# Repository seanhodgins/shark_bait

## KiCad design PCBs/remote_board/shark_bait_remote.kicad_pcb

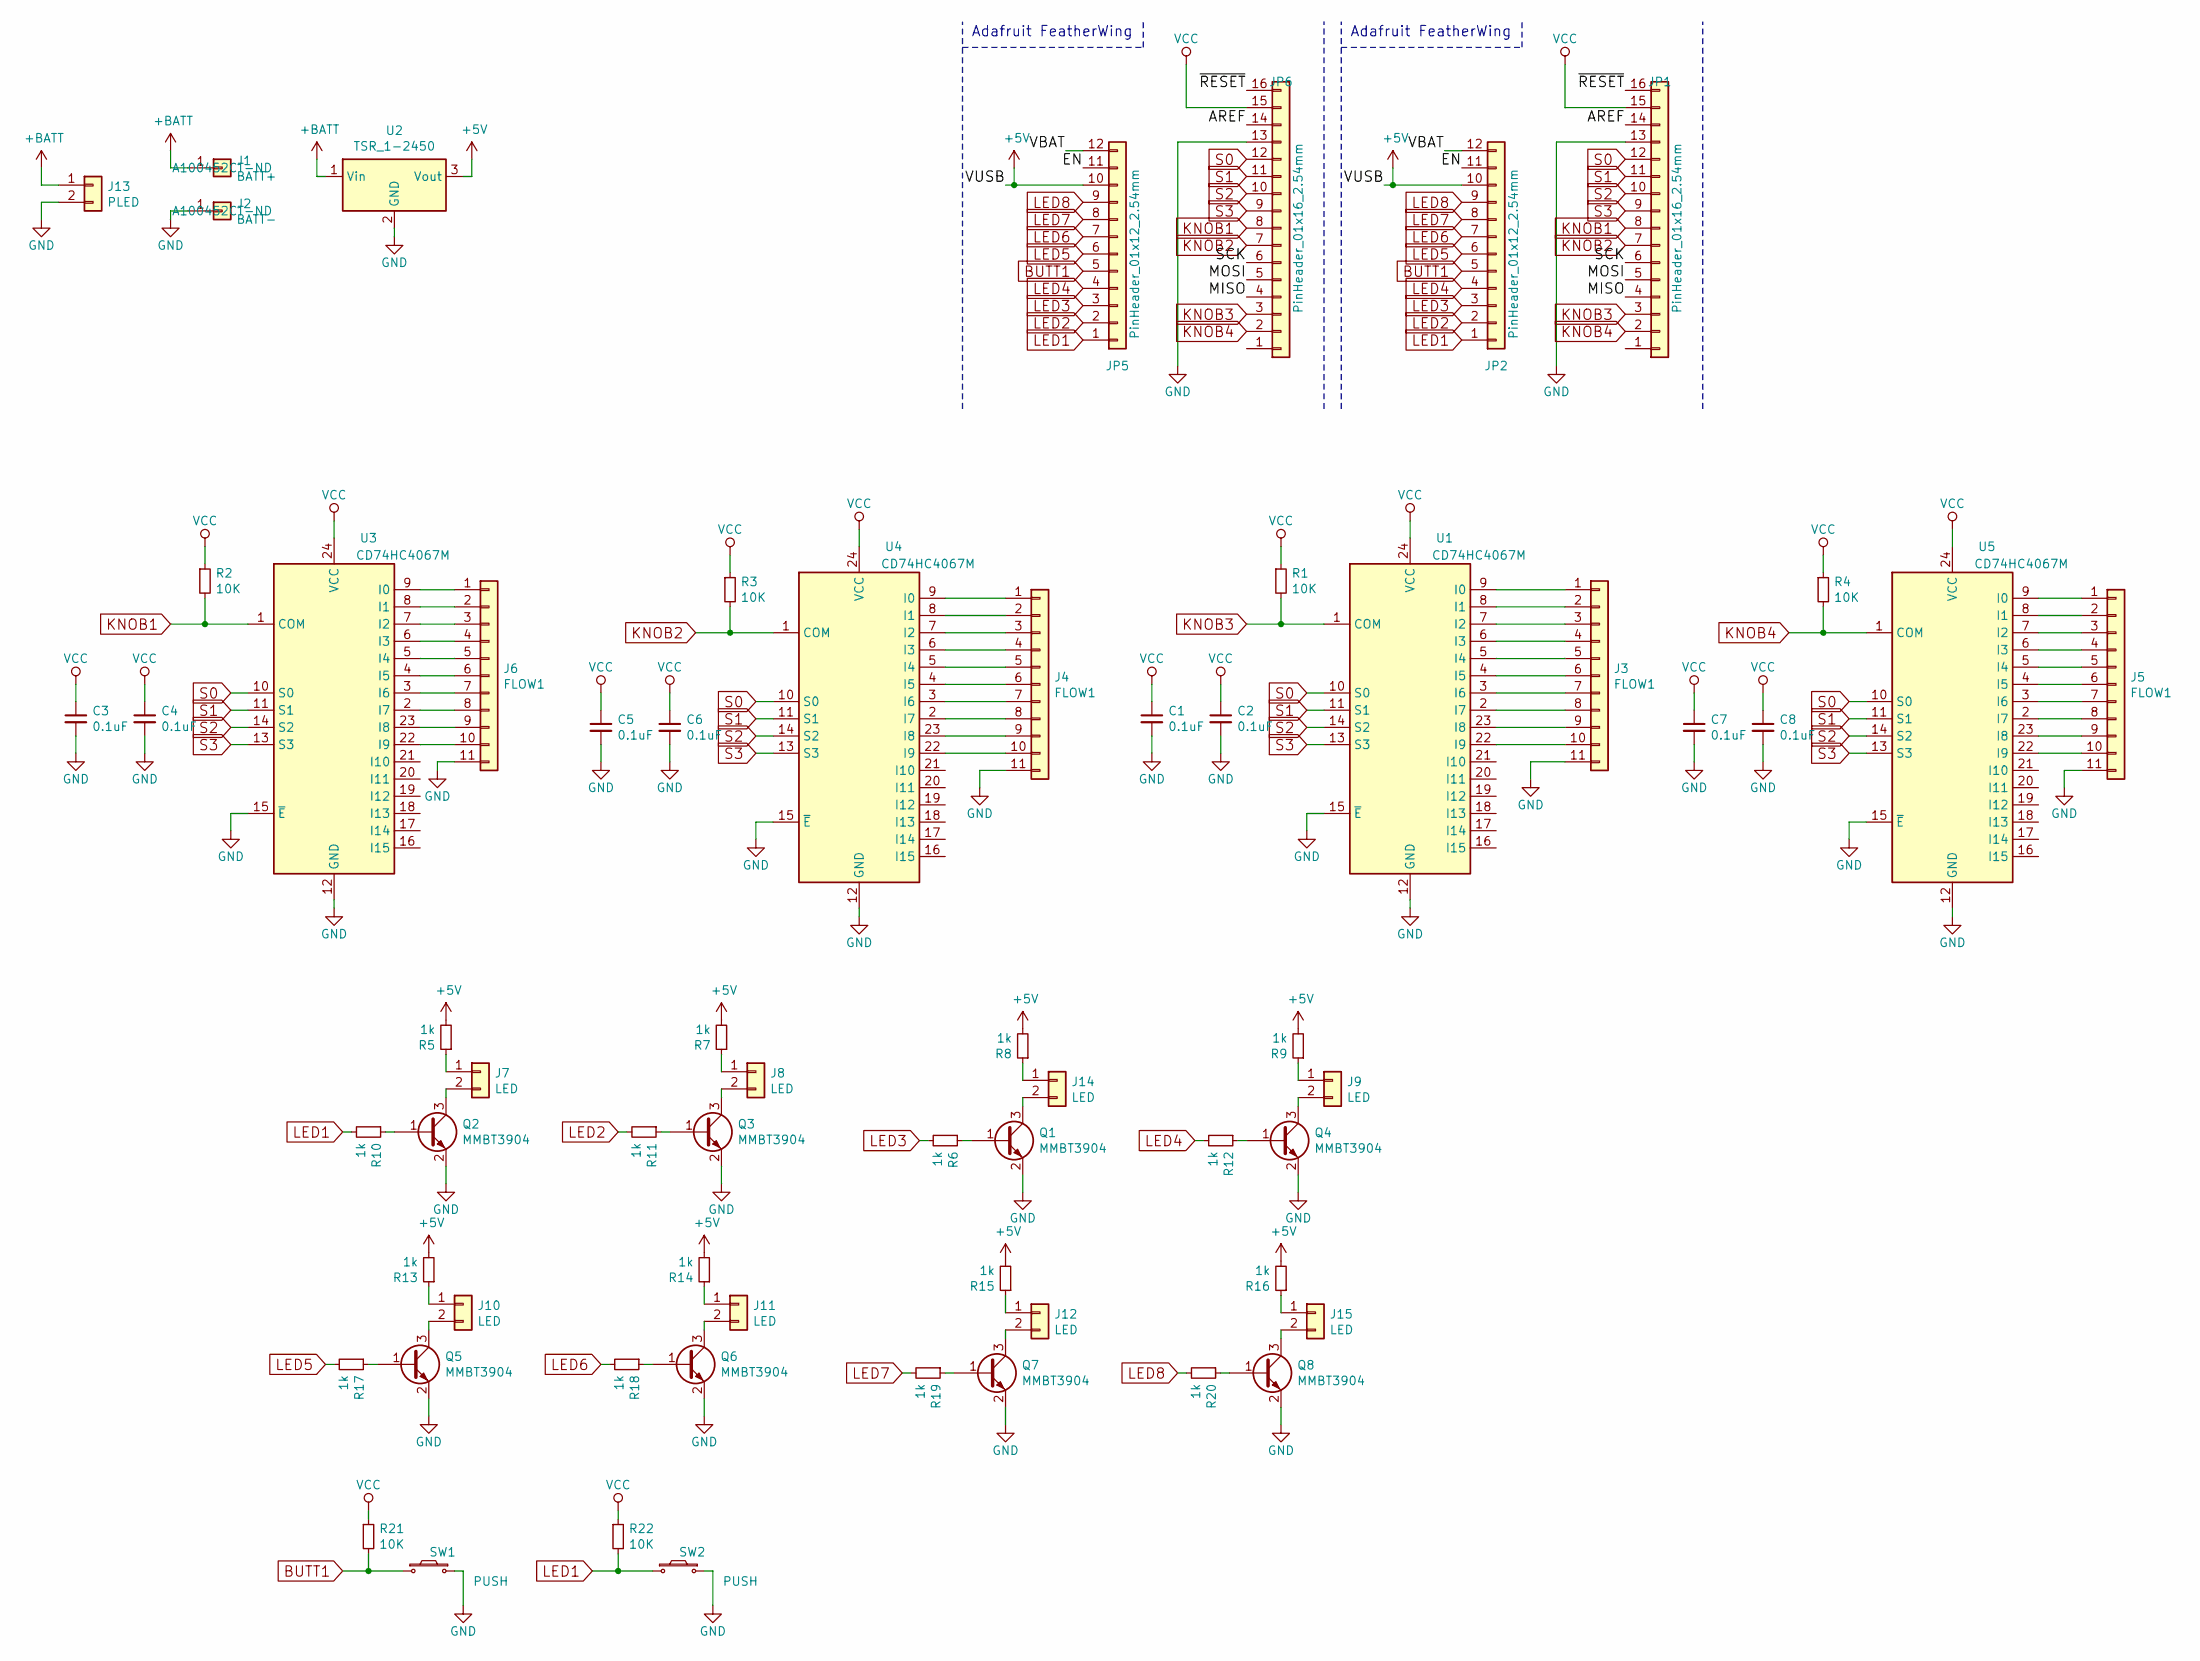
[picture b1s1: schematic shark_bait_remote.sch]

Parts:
C1, C2, C3, C4, C5, C6, C7, C8: 0.1uF; C_0805_2012Metric
J1: BATT+; connect_QC_Male; Digikey Part No. A100452CT-ND
J2: BATT-; connect_QC_Male; Digikey Part No. A100452CT-ND
J3, J4, J5, J6: FLOW1; JST_PH_B11B-PH-K_1x11_P2.00mm_Vertical
J7, J8, J9, J10, J11, J12, J14, J15: LED; JST_PH_B2B-PH-K_1x02_P2.00mm_Vertical
J13: PLED; JST_PH_B2B-PH-K_1x02_P2.00mm_Vertical
JP1, JP6: PinHeader_01x16_2.54mm; Conn_PinHeader_1x16_Reduced
JP2, JP5: PinHeader_01x12_2.54mm; Conn_PinHeader_1x12_Reduced
Q1, Q2, Q3, Q4, Q5, Q6, Q7, Q8: MMBT3904; SOT-23
R1, R2, R3, R4, R21, R22: 10K; R_0805_2012Metric
R5, R6, R7, R8, R9, R10, R11, R12, R13, R14, R15, R16, R17, R18, R19, R20: 1k; R_0805_2012Metric
SW1, SW2: PUSH; JST_PH_B2B-PH-K_1x02_P2.00mm_Vertical
U1, U3, U4, U5: CD74HC4067M; SOIC-24W_7.5x15.4mm_P1.27mm; Digikey Part No. 296-29408-1-ND
U2: TSR_1-2450; Converter_DCDC_TRACO_TSR-1_THT

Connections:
+5V: JP2.10, JP5.10, R5.2, R7.2, R8.2, R9.2, R13.2, R14.2, R15.2, R16.2, U2.3 (Vout)
+BATT: J1.1, J13.1, U2.1 (Vin)
/AREF: JP1.14, JP6.14
/EN: JP2.11, JP5.11
/MISO: JP1.4, JP6.4
/MOSI: JP1.5, JP6.5
/SCK: JP1.6, JP6.6
/VBAT: JP2.12, JP5.12
/~RESET: JP1.16, JP6.16
BUTT1: JP2.5, JP5.5, R21.2, SW1.1
GND: C1.2, C2.2, C3.2, C4.2, C5.2, C6.2, C7.2, C8.2, J2.1, J3.11, J4.11, J5.11, J6.11, J13.2, JP1.1, JP1.13, JP6.1, JP6.13, Q1.2 (E), Q2.2 (E), Q3.2 (E), Q4.2 (E), Q5.2 (E), Q6.2 (E), Q7.2 (E), Q8.2 (E), SW1.2, SW2.2, U1.12 (GND), U1.15 (~E), U2.2 (GND), U3.12 (GND), U3.15 (~E), U4.12 (GND), U4.15 (~E), U5.12 (GND), U5.15 (~E)
KNOB1: JP1.8, JP6.8, R2.2, U3.1 (COM)
KNOB2: JP1.7, JP6.7, R3.2, U4.1 (COM)
KNOB3: JP1.3, JP6.3, R1.2, U1.1 (COM)
KNOB4: JP1.2, JP6.2, R4.2, U5.1 (COM)
LED1: JP2.1, JP5.1, R10.2, R22.2, SW2.1
LED2: JP2.2, JP5.2, R11.2
LED3: JP2.3, JP5.3, R6.2
LED4: JP2.4, JP5.4, R12.2
LED5: JP2.6, JP5.6, R17.2
LED6: JP2.7, JP5.7, R18.2
LED7: JP2.8, JP5.8, R19.2
LED8: JP2.9, JP5.9, R20.2
unnamed: J3.1, U1.9 (I0)
unnamed: J3.2, U1.8 (I1)
unnamed: J3.3, U1.7 (I2)
unnamed: J3.4, U1.6 (I3)
unnamed: J3.5, U1.5 (I4)
unnamed: J3.6, U1.4 (I5)
unnamed: J3.7, U1.3 (I6)
unnamed: J3.8, U1.2 (I7)
unnamed: J3.9, U1.23 (I8)
unnamed: J3.10, U1.22 (I9)
unnamed: J4.1, U4.9 (I0)
unnamed: J4.2, U4.8 (I1)
unnamed: J4.3, U4.7 (I2)
unnamed: J4.4, U4.6 (I3)
unnamed: J4.5, U4.5 (I4)
unnamed: J4.6, U4.4 (I5)
unnamed: J4.7, U4.3 (I6)
unnamed: J4.8, U4.2 (I7)
unnamed: J4.9, U4.23 (I8)
unnamed: J4.10, U4.22 (I9)
unnamed: J5.1, U5.9 (I0)
unnamed: J5.2, U5.8 (I1)
unnamed: J5.3, U5.7 (I2)
unnamed: J5.4, U5.6 (I3)
unnamed: J5.5, U5.5 (I4)
unnamed: J5.6, U5.4 (I5)
unnamed: J5.7, U5.3 (I6)
unnamed: J5.8, U5.2 (I7)
unnamed: J5.9, U5.23 (I8)
unnamed: J5.10, U5.22 (I9)
unnamed: J6.1, U3.9 (I0)
unnamed: J6.2, U3.8 (I1)
unnamed: J6.3, U3.7 (I2)
unnamed: J6.4, U3.6 (I3)
unnamed: J6.5, U3.5 (I4)
unnamed: J6.6, U3.4 (I5)
unnamed: J6.7, U3.3 (I6)
unnamed: J6.8, U3.2 (I7)
unnamed: J6.9, U3.23 (I8)
unnamed: J6.10, U3.22 (I9)
unnamed: J7.1, R5.1
unnamed: J7.2, Q2.3 (C)
unnamed: J8.1, R7.1
unnamed: J8.2, Q3.3 (C)
unnamed: J9.1, R9.1
unnamed: J9.2, Q4.3 (C)
unnamed: J10.1, R13.1
unnamed: J10.2, Q5.3 (C)
unnamed: J11.1, R14.1
unnamed: J11.2, Q6.3 (C)
unnamed: J12.1, R15.1
unnamed: J12.2, Q7.3 (C)
unnamed: J14.1, R8.1
unnamed: J14.2, Q1.3 (C)
unnamed: J15.1, R16.1
unnamed: J15.2, Q8.3 (C)
unnamed: Q1.1 (B), R6.1
unnamed: Q2.1 (B), R10.1
unnamed: Q3.1 (B), R11.1
unnamed: Q4.1 (B), R12.1
unnamed: Q5.1 (B), R17.1
unnamed: Q6.1 (B), R18.1
unnamed: Q7.1 (B), R19.1
unnamed: Q8.1 (B), R20.1
S0: JP1.12, JP6.12, U1.10 (S0), U3.10 (S0), U4.10 (S0), U5.10 (S0)
S1: JP1.11, JP6.11, U1.11 (S1), U3.11 (S1), U4.11 (S1), U5.11 (S1)
S2: JP1.10, JP6.10, U1.14 (S2), U3.14 (S2), U4.14 (S2), U5.14 (S2)
S3: JP1.9, JP6.9, U1.13 (S3), U3.13 (S3), U4.13 (S3), U5.13 (S3)
VCC: C1.1, C2.1, C3.1, C4.1, C5.1, C6.1, C7.1, C8.1, JP1.15, JP6.15, R1.1, R2.1, R3.1, R4.1, R21.1, R22.1, U1.24 (VCC), U3.24 (VCC), U4.24 (VCC), U5.24 (VCC)

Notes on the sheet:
Adafruit FeatherWing

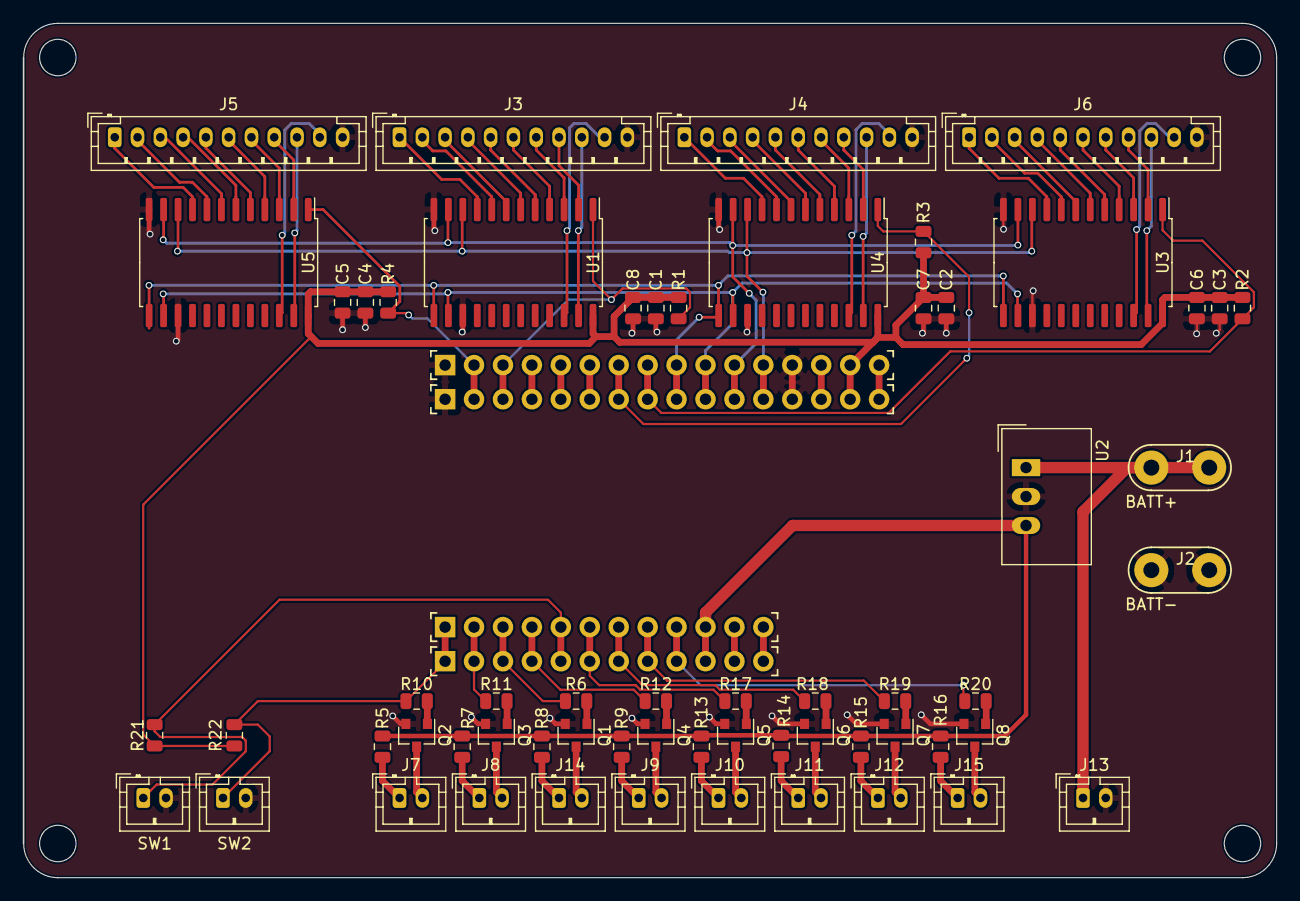
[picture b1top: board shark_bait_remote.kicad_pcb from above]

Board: 2 copper layers, 110.0 x 74.9 mm, 65 parts (0 on the bottom side), 92 nets.

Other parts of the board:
PCB**: VAL**; PCB_FeatherWing_NoHoles

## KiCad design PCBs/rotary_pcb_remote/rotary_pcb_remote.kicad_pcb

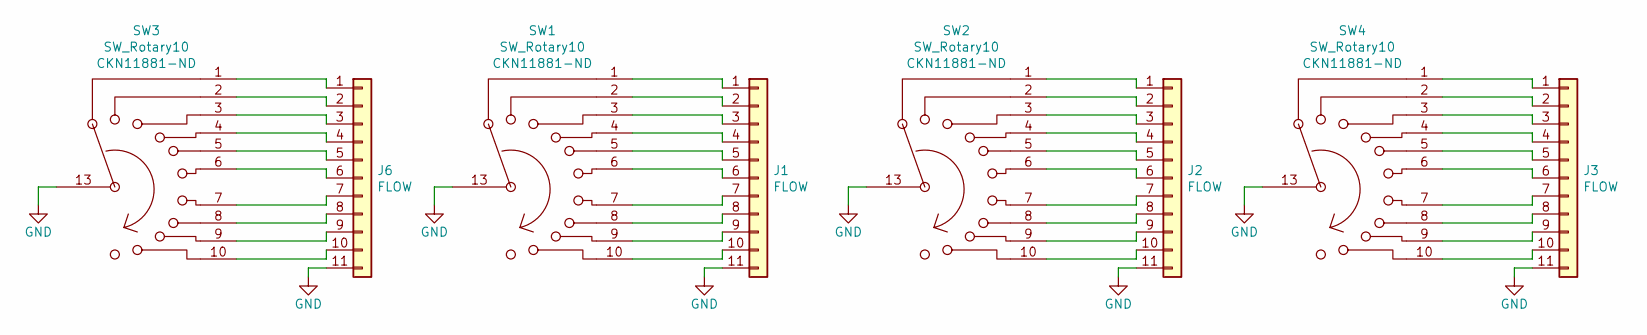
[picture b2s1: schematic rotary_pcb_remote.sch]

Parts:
J1, J2, J3, J6: FLOW; JST_PH_B11B-PH-K_1x11_P2.00mm_Vertical
SW1, SW2, SW3, SW4: SW_Rotary10; Rotary10_CK_MA00L1NCGF; Digikey Part No. CKN11881-ND

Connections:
GND: J1.11, J2.11, J3.11, J6.11, SW1.13, SW2.13, SW3.13, SW4.13
unnamed: J1.1, SW1.1
unnamed: J1.2, SW1.2
unnamed: J1.3, SW1.3
unnamed: J1.4, SW1.4
unnamed: J1.5, SW1.5
unnamed: J1.6, SW1.6
unnamed: J1.7, SW1.7
unnamed: J1.8, SW1.8
unnamed: J1.9, SW1.9
unnamed: J1.10, SW1.10
unnamed: J2.1, SW2.1
unnamed: J2.2, SW2.2
unnamed: J2.3, SW2.3
unnamed: J2.4, SW2.4
unnamed: J2.5, SW2.5
unnamed: J2.6, SW2.6
unnamed: J2.7, SW2.7
unnamed: J2.8, SW2.8
unnamed: J2.9, SW2.9
unnamed: J2.10, SW2.10
unnamed: J3.1, SW4.1
unnamed: J3.2, SW4.2
unnamed: J3.3, SW4.3
unnamed: J3.4, SW4.4
unnamed: J3.5, SW4.5
unnamed: J3.6, SW4.6
unnamed: J3.7, SW4.7
unnamed: J3.8, SW4.8
unnamed: J3.9, SW4.9
unnamed: J3.10, SW4.10
unnamed: J6.1, SW3.1
unnamed: J6.2, SW3.2
unnamed: J6.3, SW3.3
unnamed: J6.4, SW3.4
unnamed: J6.5, SW3.5
unnamed: J6.6, SW3.6
unnamed: J6.7, SW3.7
unnamed: J6.8, SW3.8
unnamed: J6.9, SW3.9
unnamed: J6.10, SW3.10

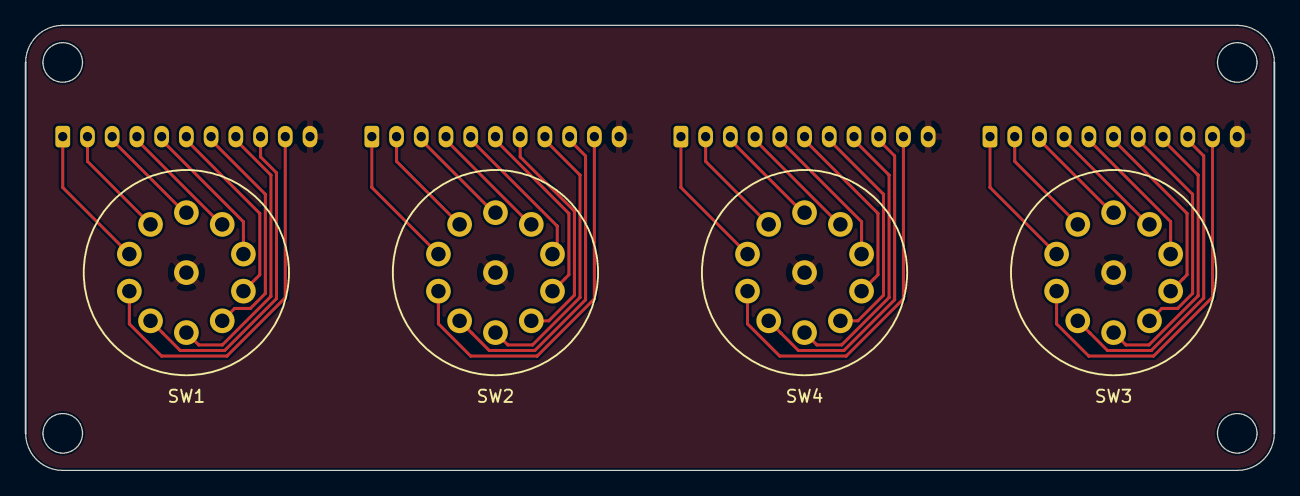
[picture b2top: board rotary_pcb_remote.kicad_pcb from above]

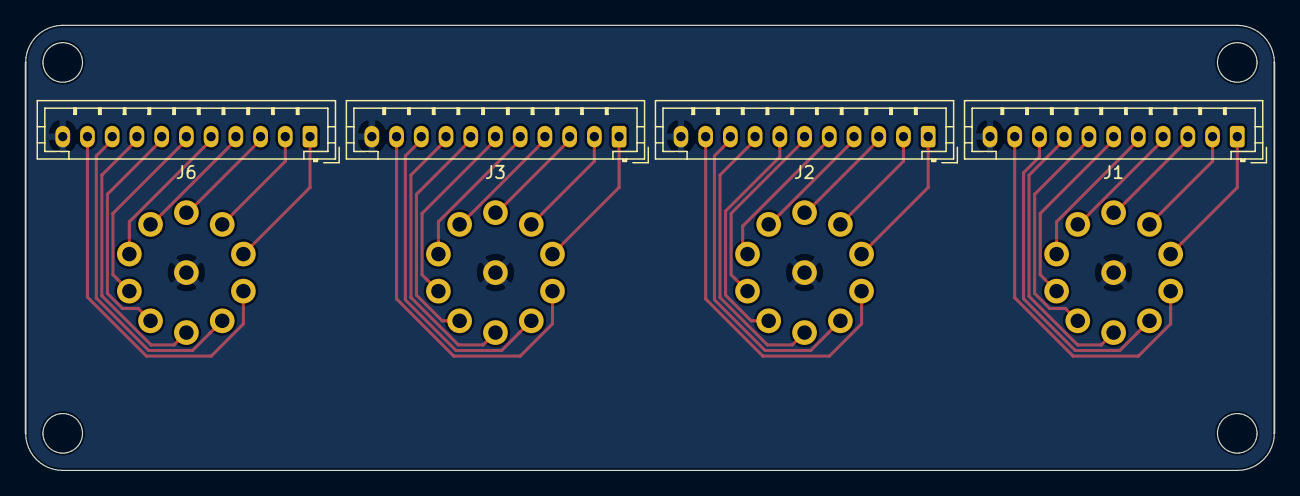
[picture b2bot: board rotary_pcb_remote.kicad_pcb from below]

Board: 2 copper layers, 101.0 x 35.9 mm, 8 parts (4 on the bottom side), 41 nets.

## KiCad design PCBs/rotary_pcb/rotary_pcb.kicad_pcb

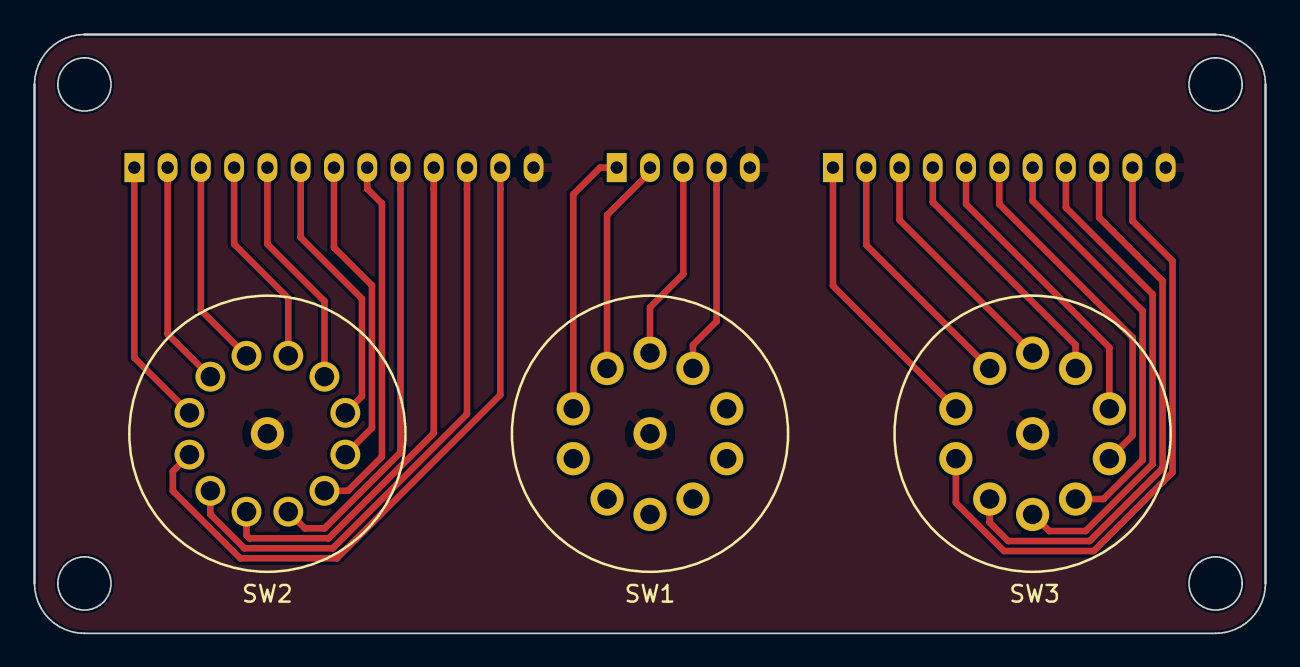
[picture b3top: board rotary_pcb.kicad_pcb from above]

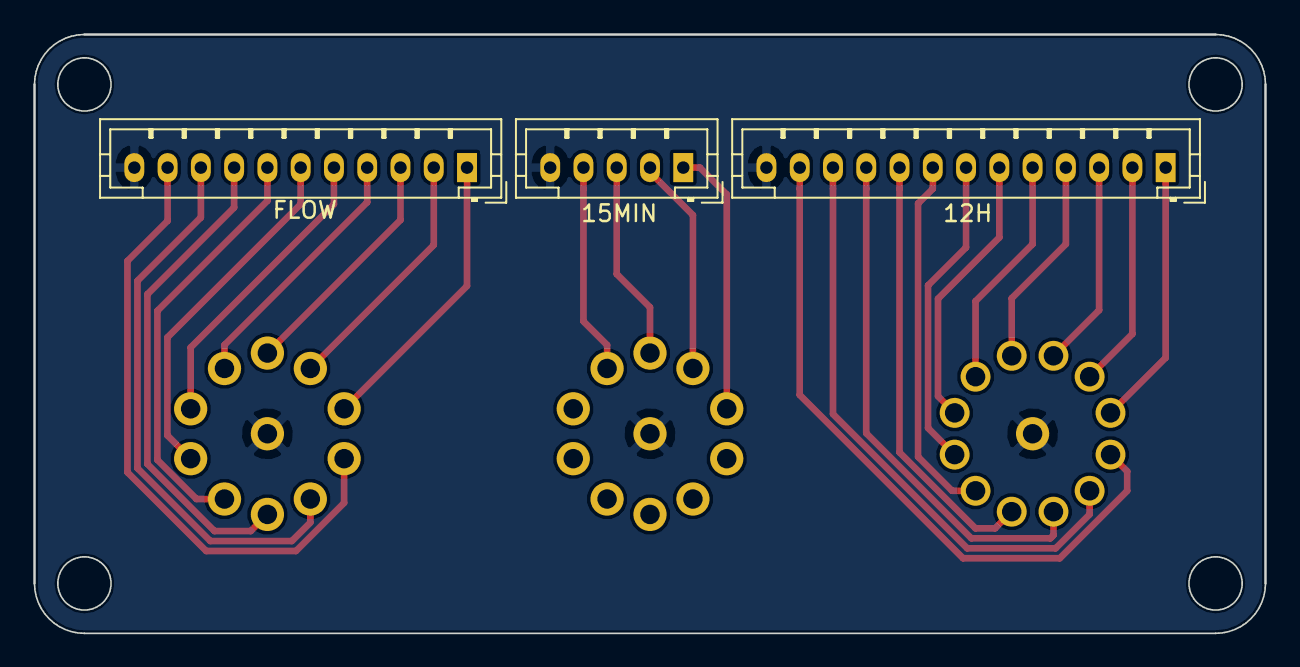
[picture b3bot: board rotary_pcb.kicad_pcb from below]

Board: 2 copper layers, 74.0 x 36.0 mm, 6 parts (3 on the bottom side), 27 nets.

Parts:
J3: 15MIN; JST_PH_B5B-PH-K_1x05_P2.00mm_Vertical
J4: 12H; JST_PH_B13B-PH-K_1x13_P2.00mm_Vertical
J6: FLOW; JST_PH_B11B-PH-K_1x11_P2.00mm_Vertical
SW1: SW_Rotary4; Rotary10_CK_MA00L1NCGF
SW2: SW_Rotary12; Rotary12_CK_MC00L1NCQF
SW3: SW_Rotary10; Rotary10_CK_MA00L1NCGF

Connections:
GND: J3.5, J4.13, J6.11, SW1.13, SW2.13, SW3.13
unnamed: J3.1, SW1.1
unnamed: J3.2, SW1.2
unnamed: J3.3, SW1.3
unnamed: J3.4, SW1.4
unnamed: J4.1, SW2.1
unnamed: J4.2, SW2.2
unnamed: J4.3, SW2.3
unnamed: J4.4, SW2.4
unnamed: J4.5, SW2.5
unnamed: J4.6, SW2.6
unnamed: J4.7, SW2.7
unnamed: J4.8, SW2.8
unnamed: J4.9, SW2.9
unnamed: J4.10, SW2.10
unnamed: J4.11, SW2.11
unnamed: J4.12, SW2.12
unnamed: J6.1, SW3.1
unnamed: J6.2, SW3.2
unnamed: J6.3, SW3.3
unnamed: J6.4, SW3.4
unnamed: J6.5, SW3.5
unnamed: J6.6, SW3.6
unnamed: J6.7, SW3.7
unnamed: J6.8, SW3.8
unnamed: J6.9, SW3.9
unnamed: J6.10, SW3.10

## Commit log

2019-05-25 updated PCBs and Ordered
2019-05-30 updated firmware
2019-05-30 Manual added
2019-05-30 STLs added
